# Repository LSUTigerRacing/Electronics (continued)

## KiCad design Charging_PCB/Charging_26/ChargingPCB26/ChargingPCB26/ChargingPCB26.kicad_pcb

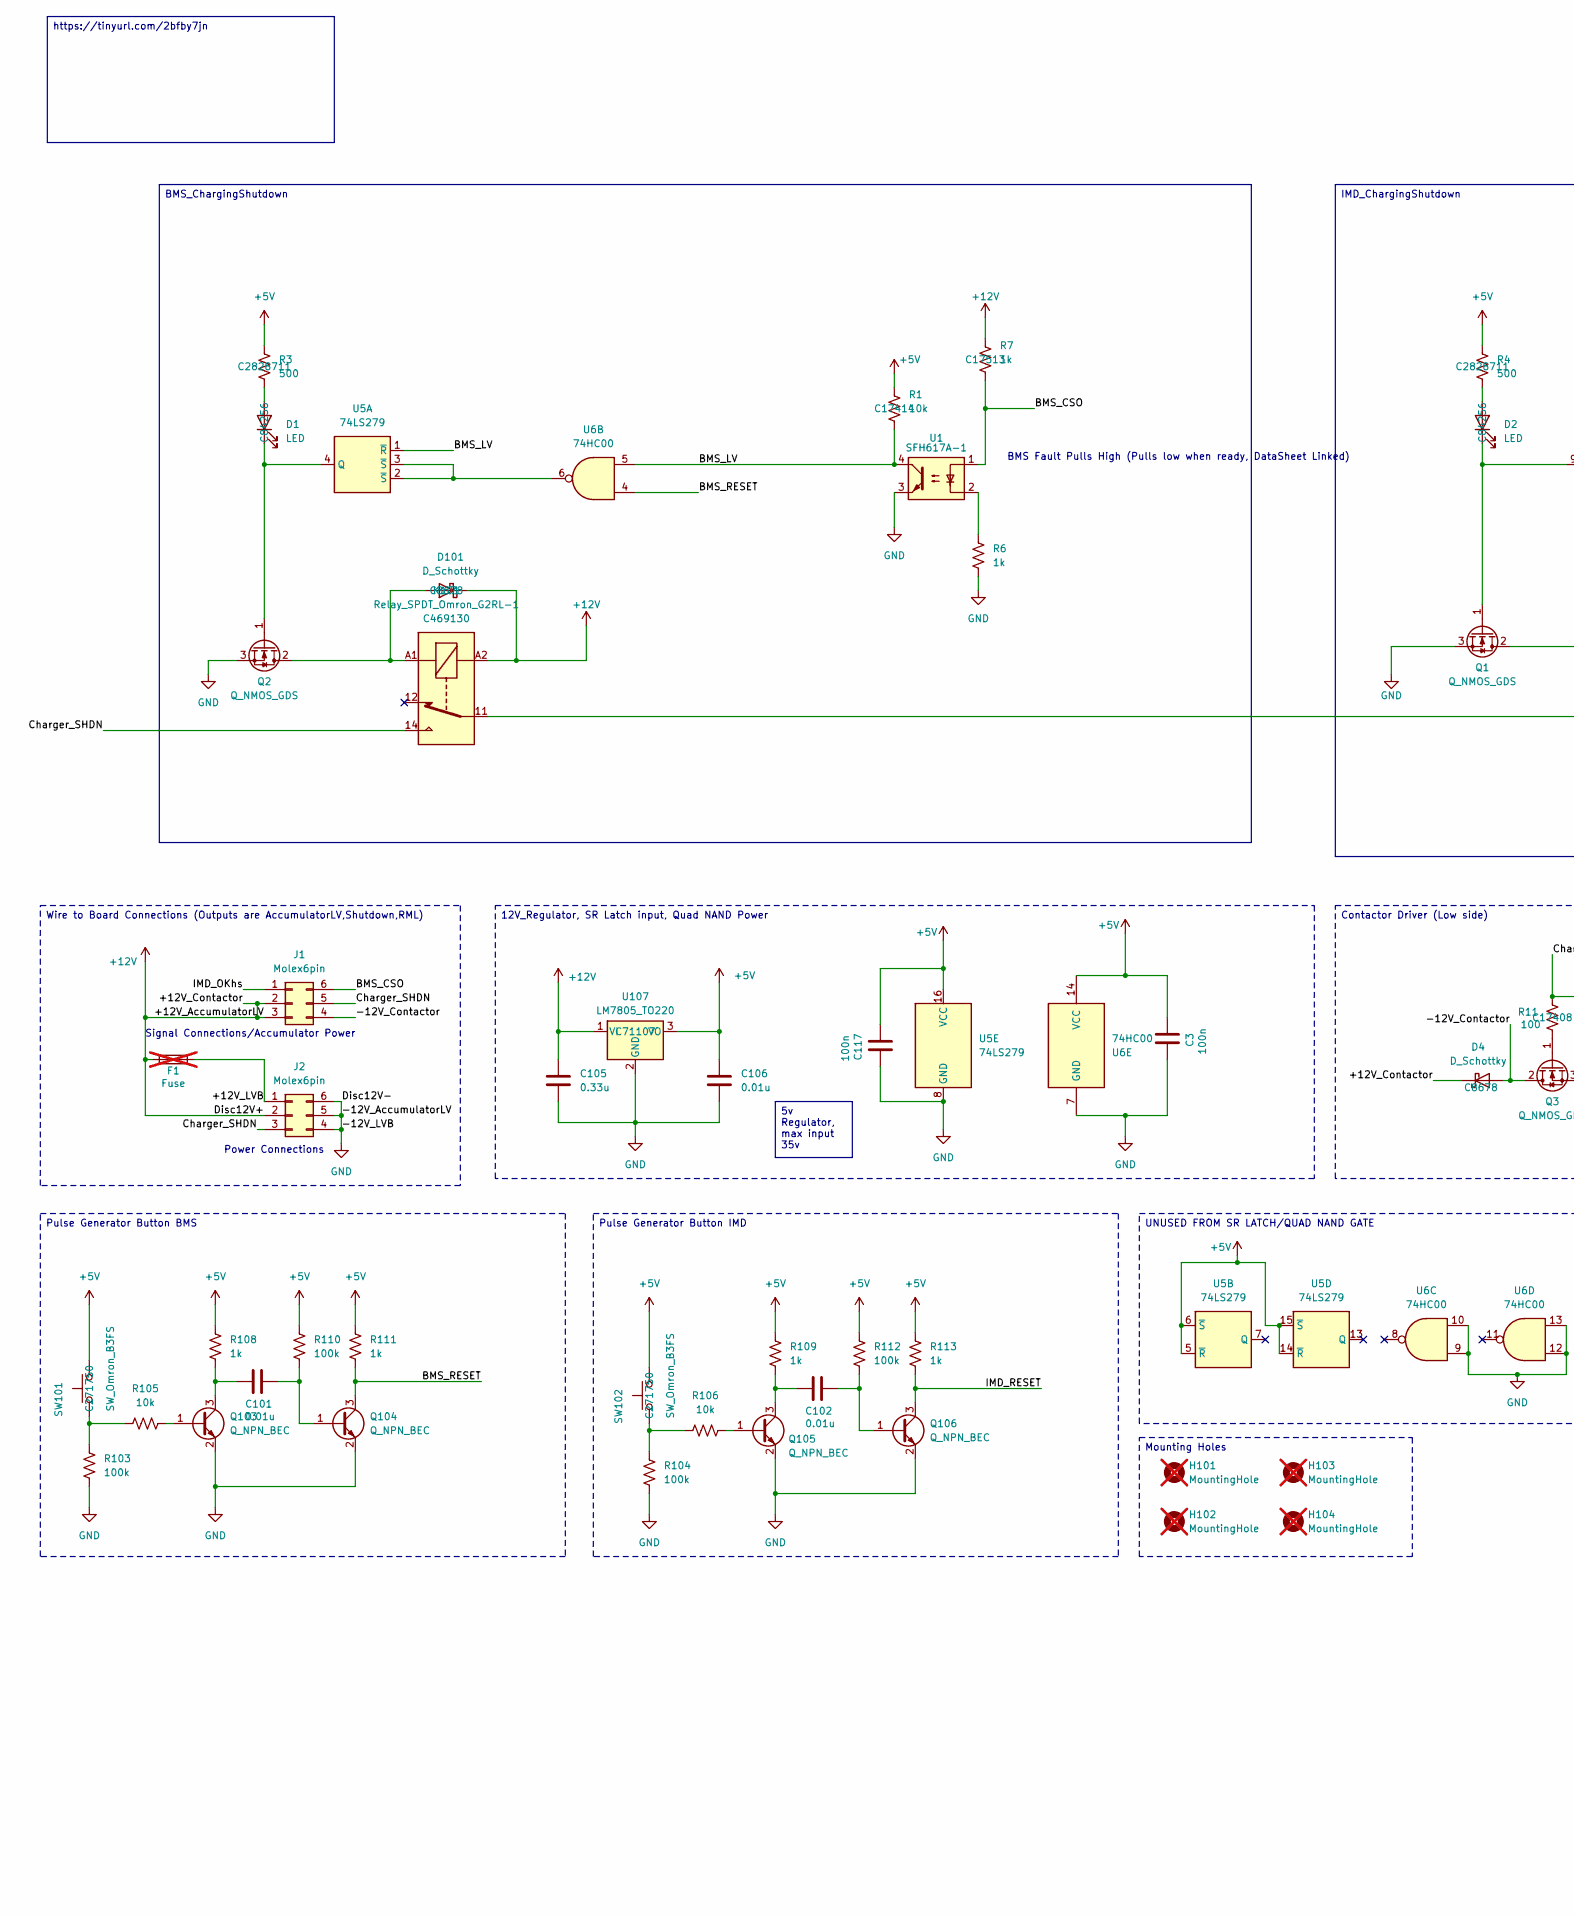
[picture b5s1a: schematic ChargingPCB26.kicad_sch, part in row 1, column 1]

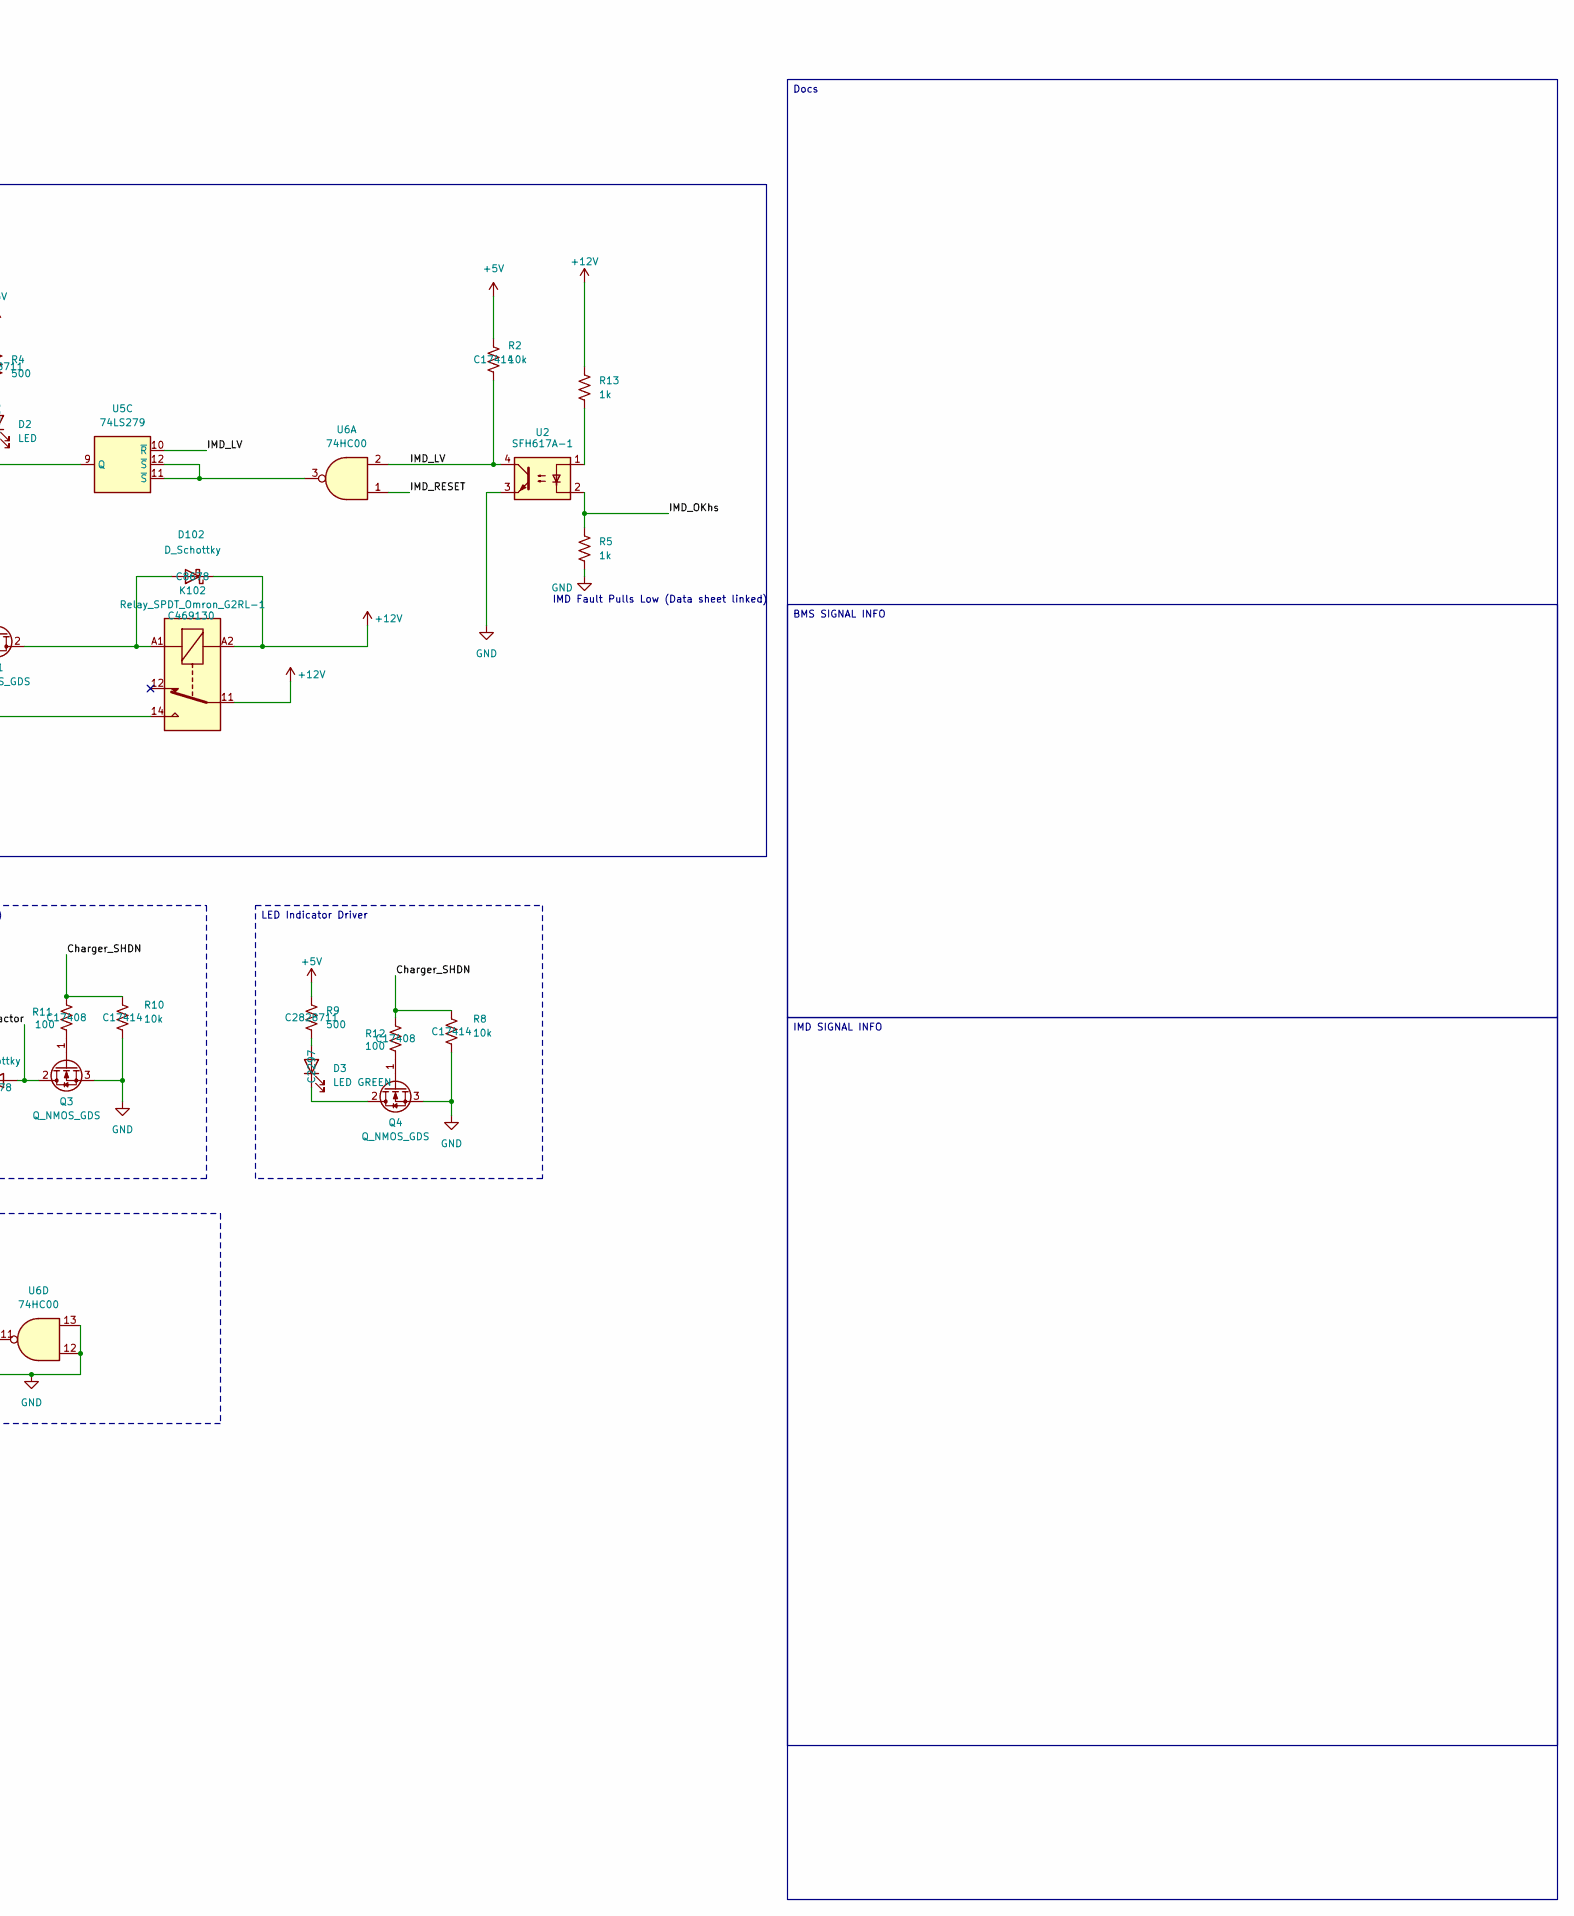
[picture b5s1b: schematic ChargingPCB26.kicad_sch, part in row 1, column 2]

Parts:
C3, C117: 100n; C_0603_1608Metric_Pad1.08x0.95mm_HandSolder; MPN CL10B104KB8NNNC; JLC# C1591
C101, C102, C106: 0.01u; C_0402_1005Metric; MPN CL05B103KB5NNNC; JLC# C15195
C105: 0.33u; C_0402_1005Metric; MPN CC0402KRX5R6BB334; JLC# C107013
D1, D2: LED; LED_0805_2012Metric_Pad1.15x1.40mm_HandSolder; MPN NCD0805R1; JLC# C84256
D3: LED GREEN; LED_0805_2012Metric_Pad1.15x1.40mm_HandSolder; MPN KT-0805G; JLC# C2297
D4, D101, D102: D_Schottky; D_SMA; MPN SS34; JLC# C8678
F1: Fuse; Fuseholder_Blade_Mini_Keystone_3568; Digikey 36-3568-ND; not fitted
H101, H102, H103, H104: MountingHole; MountingHole_2.2mm_M2; not fitted
J1, J2: Molex6pin; Molex_Nano-Fit_105314-xx06_2x03_P2.50mm_Horizontal; MPN 1053141106; Digikey WM3802-ND
K101, K102: Relay_SPDT_Omron_G2RL-1; MPN G2RL-1-DC12; JLC# C469130
Q1, Q2, Q3, Q4: Q_NMOS_GDS; TO-251-3_Vertical; JLC# C3278986
Q103, Q104, Q105, Q106: Q_NPN_BEC; SOT-23; MPN S8050 J3Y(RANGE:200-350); JLC# C2146
R1, R2, R8, R10, R105, R106: 10k; R_0805_2012Metric_Pad1.20x1.40mm_HandSolder; MPN 0805W8F1002T5E; JLC# C17414
R3, R4, R9: 500; R_0805_2012Metric_Pad1.20x1.40mm_HandSolder; MPN ARG05BTC5000; JLC# C2828711
R5, R6, R13: 1k; R_0805_2012Metric_Pad1.20x1.40mm_HandSolder; MPN 0805W8F1001T5E; Digikey 1.00KXBK-ND
R7, R108, R109, R111, R113: 1k; R_0805_2012Metric_Pad1.20x1.40mm_HandSolder; MPN 0805W8F1001T5E; JLC# C17513
R11, R12: 100; R_0805_2012Metric_Pad1.20x1.40mm_HandSolder; JLC# C17408
R103, R104, R110, R112: 100k; R_0805_2012Metric_Pad1.20x1.40mm_HandSolder; MPN 0805W8F1003T5E; JLC# C149504
SW101, SW102: SW_Omron_B3FS; SW_SPST_Omron_B3FS-100xP; MPN B3FS-1000P; JLC# C271750
U1, U2: SFH617A-1; DIP-4_W7.62mm; MPN PC817X2NSZW; Digikey 58-SFH615A-1X-ND
U5: 74LS279; DIP-16_W7.62mm; MPN SN74LS279AN; Digikey 296-3684-5-ND
U6: 74HC00; DIP-14_W7.62mm; MPN SN74HC00N; JLC# C2902
U107: LM7805_TO220; TO-220-3_Vertical; MPN LM7805L-TF3-T; JLC# C71107

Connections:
+5V: C3.1, C106.1, C117.1, R1.1, R2.1, R3.1, R4.1, R9.1, R108.1, R109.1, R110.1, R111.1, R112.1, R113.1, SW101.2, SW102.2, U5.5 (~R), U5.6 (~S), U5.14 (~R), U5.15 (~S), U5.16 (VCC), U6.14 (VCC), U107.3 (VO)
+12V: C105.1, D4.1 (K), D101.1 (K), D102.1 (K), F1.1, J1.2, J1.3, J2.2, K101.A2, K102.11, K102.A2, R7.1, R13.1, U107.1 (VI)
/+12V_LVB: F1.2, J2.1
/-12V_Contactor: D4.2 (A), J1.4, Q3.2 (D)
/BMS_CSO: J1.6, R7.2, U1.1
/BMS_LV: R1.2, U1.4, U5.1 (~R), U6.5
/BMS_RESET: Q104.3 (C), R111.2, U6.4
/Charger_SHDN: J1.5, J2.3, K101.14, R8.1, R10.1, R11.1, R12.1
/IMD_LV: R2.2, U2.4, U5.10 (~R), U6.2
/IMD_OKhs: J1.1, R5.1, U2.2
/IMD_RESET: Q106.3 (C), R113.2, U6.1
GND: C3.2, C105.2, C106.2, C117.2, J2.4, J2.5, J2.6, Q1.3 (S), Q2.3 (S), Q3.3 (S), Q4.3 (S), Q103.2 (E), Q104.2 (E), Q105.2 (E), Q106.2 (E), R5.2, R6.2, R8.2, R10.2, R103.2, R104.2, U1.3, U2.3, U5.8 (GND), U6.7 (GND), U6.9, U6.10, U6.12, U6.13, U107.2 (GND)
unnamed: D1.2 (A), R3.2
unnamed: D1.1 (K), Q2.1 (G), U5.4 (Q)
unnamed: D2.2 (A), R4.2
unnamed: D2.1 (K), Q1.1 (G), U5.9 (Q)
unnamed: D3.2 (A), R9.2
unnamed: D3.1 (K), Q4.2 (D)
unnamed: D101.2 (A), K101.A1, Q2.2 (D)
unnamed: D102.2 (A), K102.A1, Q1.2 (D)
unnamed: K101.11, K102.14
unnamed: Q3.1 (G), R11.2
unnamed: Q4.1 (G), R12.2
unnamed: Q103.1 (B), R105.1
unnamed: C101.1, Q103.3 (C), R108.2
unnamed: C101.2, Q104.1 (B), R110.2
unnamed: Q105.1 (B), R106.1
unnamed: C102.1, Q105.3 (C), R109.2
unnamed: C102.2, Q106.1 (B), R112.2
unnamed: R6.1, U1.2
unnamed: R13.2, U2.1
unnamed: R103.1, R105.2, SW101.1
unnamed: R104.1, R106.2, SW102.1
unnamed: U5.2 (~S), U5.3 (~S), U6.6
unnamed: U5.11 (~S), U5.12 (~S), U6.3

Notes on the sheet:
Power Connections
Signal Connections/Accumulator Power
BMS Fault Pulls High (Pulls low when ready, DataSheet Linked)
IMD Fault Pulls Low (Data sheet linked)
Contactor Driver (Low side)
IMD SIGNAL INFO
UNUSED FROM SR LATCH/QUAD NAND GATE
5v Regulator, max input 35v
Mounting Holes
BMS SIGNAL INFO
BMS_ChargingShutdown
Pulse Generator Button BMS
Docs
IMD_ChargingShutdown
LED Indicator Driver
12V_Regulator, SR Latch input, Quad NAND Power
Wire to Board Connections (Outputs are AccumulatorLV,Shutdown,RML)
Pulse Generator Button IMD
https://tinyurl.com/2bfby7jn

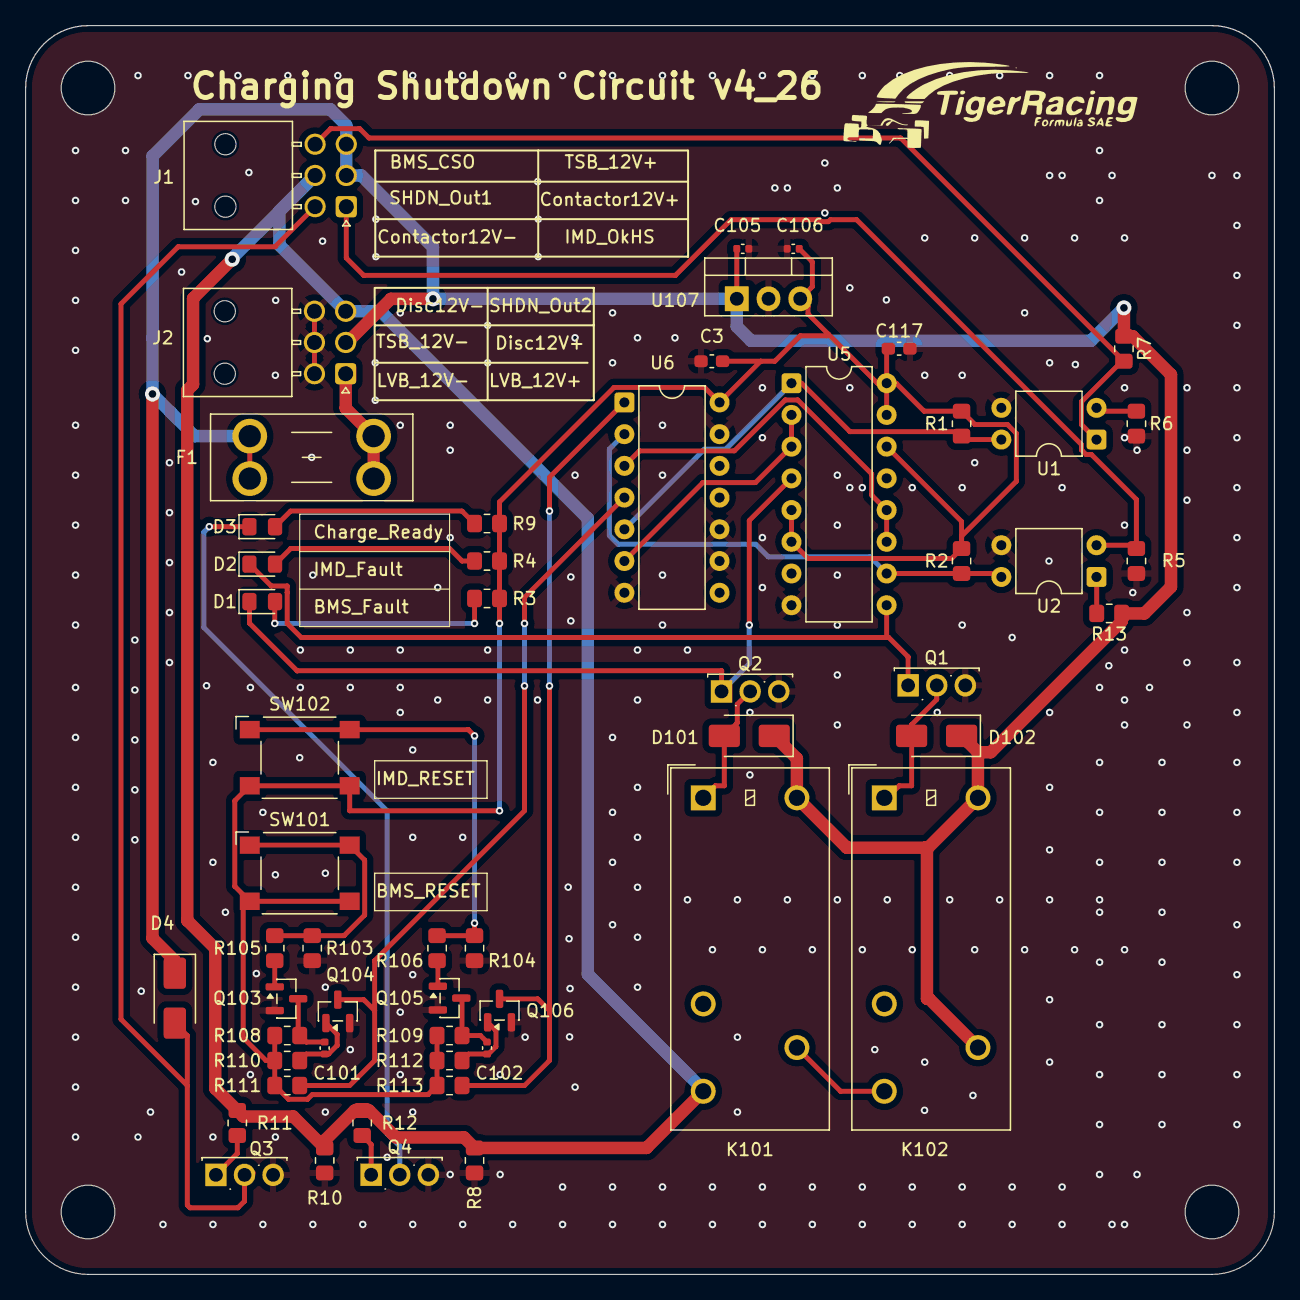
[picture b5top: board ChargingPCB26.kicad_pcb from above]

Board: 2 copper layers, 100.0 x 100.0 mm, 59 parts (0 on the bottom side), 35 nets.
